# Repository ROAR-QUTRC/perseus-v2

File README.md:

> [!WARNING]
> This repository is now archived please see [perseus-v3](https://github.com/ROAR-QUTRC/perseus-v3/).

# perseus-v2

The main codebase for perseus starting 2024

## Documentation

Full documentation is located [here](https://roar-qutrc.github.io/)

## CI/CD Status

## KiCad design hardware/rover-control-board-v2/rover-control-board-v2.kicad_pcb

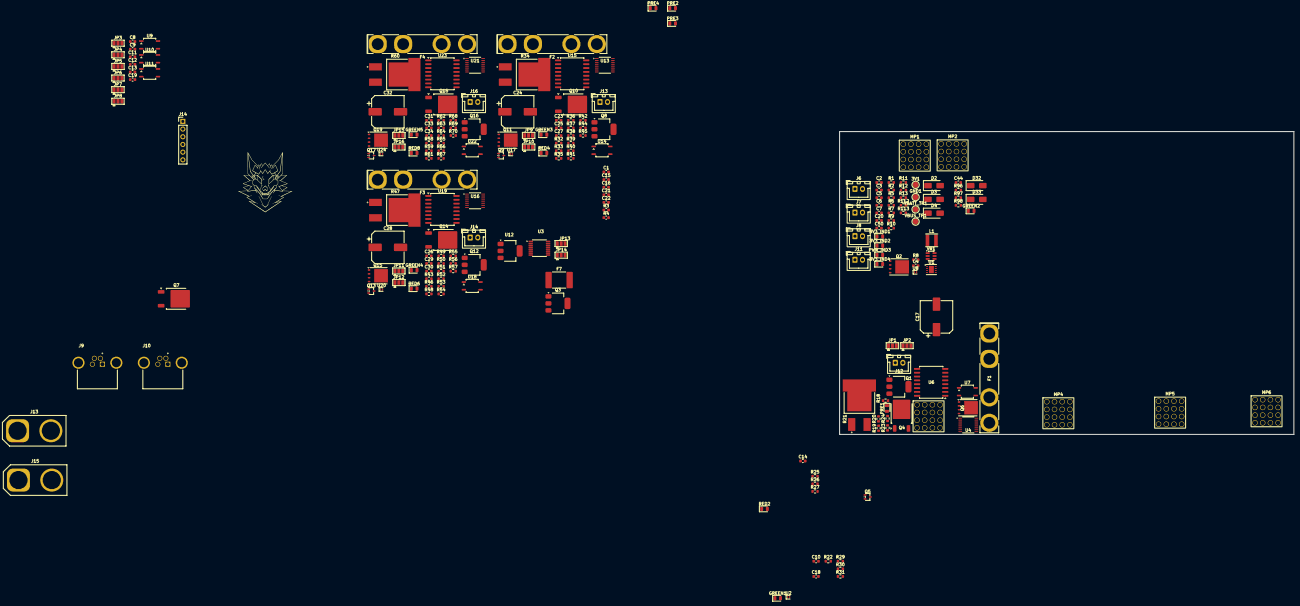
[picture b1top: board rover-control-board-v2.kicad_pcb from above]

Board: 4 copper layers, 150.0 x 100.0 mm, 216 parts (0 on the bottom side), 123 nets, no tracks yet.

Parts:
3V1: Testpoint; TestPoint_Pad_D2.0mm
3V3_IND1, 3V3_IND2, 3V3_IND4: 350-599; LED_0805_2012Metric
C1, C50: 4.7nF; C_0603_1608Metric
C2, C12, C13, C19: 10uF; C_0603_1608Metric
C3, C8, C9, C11, C16: 1uF; C_0603_1608Metric
C4, C5, C10, C14, C15, C18, C20, C23, C25, C26, C27, C29, C30, C31, C33, C34: 100nF; C_0603_1608Metric
C6, C7, C21, C22: 22uF; C_0603_1608Metric
C17, C24, C28, C32: C_Polarized; CP_Elec_10x10.5
C44: 10nF; C_0603_1608Metric
D2, D3: B160-E3; D_SMA
D4: 60V TVS; D_SMA
D32: US1M; D_SMA
D33: SMAZ12-13-F; D_SMA
F1, F2, F3, F4: Blade; Fuseholder_Keystone_3555-2
F7: 2A; Fuse_2920_7451Metric_Pad2.10x5.45mm_HandSolder
GND1: Testpoint; TestPoint_Pad_D2.0mm
GREEN1, GREEN2, GREEN3, GREEN4, GREEN5: 350-599; LED_0805_2012Metric
J6, J7, J8: CAN1; JST_XH_B2B-XH-A_1x02_P2.50mm_Vertical
J9, J10: M8 receptacle; Tensility_M8_Socket_4P_Shielded_A
J11: Contactor; JST_XH_B2B-XH-A_1x02_P2.50mm_Vertical
J12, J13#2, J14, J16: TEMP_PROBE; JST_XH_B2B-XH-A_1x02_P2.50mm_Vertical
J13: XT90; AMASS_XT90-F_1x02_P11.00mm_Vertical
J14#2: EXT_I_SENSE; PinHeader_1x06_P2.54mm_Vertical
J15: XT90_PWR; AMASS_XT90-F_1x02_P11.00mm_Vertical
JP1, JP9, JP11, JP15: ADDR1; SolderJumper-3_P1.3mm_Open_Pad1.0x1.5mm
JP2, JP10, JP12, JP16: ADDR2; SolderJumper-3_P1.3mm_Open_Pad1.0x1.5mm
JP3, JP4, JP5, JP6, JP7, JP8, JP13, JP14: ADDR; SolderJumper-3_P1.3mm_Open_Pad1.0x1.5mm
L1: HPC4018NF-4R7M; L_Taiyo-Yuden_MD-4040
MP1, MP2, MP3, MP4, MP5, MP6: Redcube Press Fit; MP_Wurth_WP-BUFU_7461097
PRE1, PRE2, PRE3, PRE4: 5991110147F; LED_0805_2012Metric
PWR_IND3: 350-599; LED_0805_2012Metric
Q1, Q3, Q8, Q12, Q16: NMOS_GDS; SOT-223
Q2, Q6, Q11, Q15, Q19: CSD19533Q5A; TDSON-8-1
Q4, Q7, Q10, Q14, Q18: Q_PMOS_GDS; TO-252-2
Q5, Q9, Q13, Q17: PMOS; SOT-323_SC-70
R1, R2: 223k; R_0603_1608Metric
R3, R4: 62R; C_0603_1608Metric
R5, R23, R24, R30, R37, R38, R45, R50, R51, R57, R63, R64, R70: 1k; R_0603_1608Metric
R6, R29, R44, R56, R69: 20k; R_0603_1608Metric
R7: 109k; R_0603_1608Metric
R8: 10k; C_0603_1608Metric
R9: 9.53M; R_0603_1608Metric
R10: 232k; R_0603_1608Metric
R11, R12, R20, R35, R48, R61, R97: 4.7k; R_0603_1608Metric
R13, R18, R25, R27, R31, R32, R36, R40, R41, R43, R49, R53, R54, R58, R62, R66, R67, R98: 10k; R_0603_1608Metric
R19, R26, R33, R39, R46, R52, R59, R65, R96: 100R; R_0603_1608Metric
R21, R34, R47, R60: 10R; RES_PWR263S-35-10R0F
R22, R42, R55, R68: 200R; R_0603_1608Metric
R112, R113: 62R; R_0603_1608Metric
RED2, RED4, RED6, RED8: 5991110147F; LED_0805_2012Metric
U1: max6496
U2, U8, U17, U20, U24: D3V3M1U2S9-7; D_SOD-882
U3: ADC128D818; TSSOP-16_4.4x5mm_P0.65mm
U4, U13, U16, U21: LM82
U6, U15, U19, U23: ACS37003; SOIC-16W_7.5x10.3mm_P1.27mm
U7, U14, U18, U22: VOM1271T; SOP-4_3.8x4.1mm_P2.54mm
U9, U10, U11: MCP3427T-E/UN; SOP-4_3.8x4.1mm_P2.54mm
U12: MCP1792x-5002xDB; SOT-223-3_TabPin2
VBATT_TP1: Testpoint; TestPoint_Pad_D2.0mm
VBUS_TP1: Testpoint; TestPoint_Pad_D2.0mm
VR1: AP63203WU-7; TSOT-23-6

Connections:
3V3: 3V1.1 (1_1), 3V3_IND1.2 (A), C6.1, C7.1, C8.2, C9.2, C11.2, C12.2, C13.2, C15.2, C16.1, C19.2, JP3.1 (A), JP4.1 (A), JP5.1 (A), JP6.1 (A), JP7.1 (A), JP8.1 (A), JP13.1 (A), JP14.1 (A), L1.2, R11.2, R12.2, U3.5 (V+), VR1.1 (FB)
+BATT: C28.1, D4.2 (A2), J15.2, MP1.1 (1_1), PWR_IND3.2 (A), Q15.5 (D), R6.2, R47.1, VBATT_TP1.1 (1_1)
/3v3: C14.2, C18.2, C23.2, C25.2, C26.2, C29.2, C31.2, C33.2, J14#2.6, JP1.1 (A), JP2.1 (A), JP9.1 (A), JP10.1 (A), JP11.1 (A), JP12.1 (A), JP15.1 (A), JP16.1 (A), RED2.2 (A), RED4.2 (A), RED6.2 (A), RED8.2 (A), U4.2 (VCC), U6.13 (VCC), U13.2 (VCC), U15.13 (VCC), U16.2 (VCC), U19.13 (VCC), U21.2 (VCC), U23.13 (VCC)
/CAN_H: J6.1, J7.1, J8.1, J10.2
/CAN_L: J6.2, J7.2, J8.2, J10.1
/JMP_PWR: C21.1, U12.1 (VI)
/SCLK: R11.1, U4.14 (SCLK), U13.14 (SCLK), U16.14 (SCLK), U21.14 (SCLK)
/SDATA: R12.1, U4.12 (SDATA), U13.12 (SDATA), U16.12 (SDATA), U21.12 (SDATA)
/TEMP_ALARM_: R26.2, R39.2, R52.2, R65.2, U4.16 (T_ALARM), U13.16 (T_ALARM), U16.16 (T_ALARM), U21.16 (T_ALARM)
/VBATT_sense: C20.2, R5.2, R6.1, U8.1 (K)
/aux_1_ctrl: GREEN3.2 (A), R42.1
/aux_1_pre_en: PRE2.2 (A), R33.1
/aux_1_v_sense: C27.1, R44.1, R45.2, U17.1 (K)
/comp_ctrl: GREEN1.2 (A), R22.1
/comp_pre_en: PRE1.2 (A), R19.1
/comp_v_sense: C10.1, R29.1, R30.2, U2.1 (K)
/comp_vi_out: U6.12 (VIOUT), U9.1 (CH1+)
/comp_vi_vref: U6.11 (VREF), U9.2 (CH1-)
/contactor/COIL_H: D32.1 (K), F7.2, GREEN2.2 (A), J11.1
/contactor/COIL_L: D33.1 (K), J11.2, Q3.2 (D), R98.2
/drive_1_ctrl: GREEN4.2 (A), R55.1
/drive_1_pre_en: PRE3.2 (A), R46.1
/drive_1_v_sense: C30.1, R56.1, R57.2, U20.1 (K)
/ext_ctrl: GREEN5.2 (A), R68.1
/ext_pre_en: PRE4.2 (A), R59.1
/power_bus_1/PWR_OUT: F1.1, J13.1, MP3.1 (1_1), Q4.3 (S), R29.2
/power_bus_2/PWR_OUT: F2.1, MP4.1 (1_1), Q10.3 (S), R44.2
/power_bus_3/PWR_OUT: F3.1, MP5.1 (1_1), Q14.3 (S), R56.2
/power_bus_4/PWR_OUT: F4.1, MP6.1 (1_1), Q18.3 (S), R69.2
/power_bus_4/V_sense: C34.1, R69.1, R70.2, U24.1 (K)
GND: C1.2, C2.2, C3.2, C4.2, C6.2, C7.2, C8.1, C9.1, C10.2, C11.1, C12.1, C13.1, C14.1, C15.1, C16.2, C17.2, C18.1, C19.1, C20.1, C21.2, C22.2, C23.1, C24.2, C25.1, C26.1, C27.2, C28.2, C29.1, C30.2, C31.1, C32.2, C33.1, C34.2, C44.2, C50.2, D4.1 (A1), GND1.1 (1_1), J13.2, J14#2.1, J15.1, JP1.3 (B), JP2.3 (B), JP3.3 (B), JP4.3 (B), JP5.3 (B), JP6.3 (B), JP7.3 (B), JP8.3 (B), JP9.3 (B), JP10.3 (B), JP11.3 (B), JP12.3 (B), JP13.3 (B), JP14.3 (B), JP15.3 (B), JP16.3 (B), Q1.3 (S), Q3.3 (S), Q5.3 (S), Q8.3 (S), Q9.3 (S), Q12.3 (S), Q13.3 (S), Q16.3 (S), Q17.3 (S), R1.2, R2.2, R5.1, R7.2, R10.2, R13.2, R18.1, R20.1, R27.2, R30.1, R31.1, R32.1, R35.1, R40.2, R41.1, R43.1, R45.1, R48.1, R53.2, R54.1, R57.1, R58.1, R61.1, R66.2, R67.1, R70.1, R97.1, U1.5 (GND), U2.2 (A), U3.4 (GND), U4.8 (GND), U6.16 (GND), U7.2, U8.2 (A), U9.3 (V_{SS}), U10.3 (V_{SS}), U11.3 (V_{SS}), U12.2 (GND), U13.8 (GND), U14.2, U15.16 (GND), U16.8 (GND), U17.2 (A), U18.2, U19.16 (GND), U20.2 (A), U21.8 (GND), U22.2, U23.16 (GND), U24.2 (A), VR1.4 (GND)
unnamed: 3V3_IND1.1 (K), R13.1
unnamed: 3V3_IND2.1 (K), R1.1
unnamed: 3V3_IND4.2 (A), C22.1, D3.2 (A), U12.3 (VO)
unnamed: 3V3_IND4.1 (K), R2.1
unnamed: C1.1, R3.1, R4.1
unnamed: C50.1, R112.1, R113.1
unnamed: C3.1, D2.1 (K), D3.1 (K)
unnamed: D32.2 (A), D33.2 (A)
unnamed: F1.2, U6.5 (IP-), U6.6 (IP-), U6.7 (IP-), U6.8 (IP-)
unnamed: F2.2, U15.5 (IP-), U15.6 (IP-), U15.7 (IP-), U15.8 (IP-)
unnamed: F3.2, U19.5 (IP-), U19.6 (IP-), U19.7 (IP-), U19.8 (IP-)
unnamed: F4.2, U23.5 (IP-), U23.6 (IP-), U23.7 (IP-), U23.8 (IP-)
unnamed: GREEN1.1 (K), R31.2
unnamed: GREEN2.1 (K), R98.1
unnamed: GREEN3.1 (K), R41.2
unnamed: GREEN4.1 (K), R54.2
unnamed: GREEN5.1 (K), R67.2
unnamed: J9.1, R112.2
unnamed: J9.2, R113.2
unnamed: J12.1, U4.4 (D-)
unnamed: J12.2, U4.3 (D+)
unnamed: J13#2.1, U13.4 (D-)
unnamed: J13#2.2, U13.3 (D+)
unnamed: J14.1, U16.4 (D-)
unnamed: J14.2, U16.3 (D+)
unnamed: J16.1, U21.4 (D-)
unnamed: J16.2, U21.3 (D+)
unnamed: JP1.2 (C), U4.10 (ADDR0)
unnamed: JP2.2 (C), U4.6 (ADDR1)
unnamed: JP9.2 (C), U13.10 (ADDR0)
unnamed: JP10.2 (C), U13.6 (ADDR1)
unnamed: JP11.2 (C), U16.10 (ADDR0)
unnamed: JP12.2 (C), U16.6 (ADDR1)
unnamed: JP13.2 (C), U3.8 (A1)
unnamed: JP14.2 (C), U3.7 (A0)
unnamed: JP15.2 (C), U21.10 (ADDR0)
unnamed: JP16.2 (C), U21.6 (ADDR1)
unnamed: PRE1.1 (K), R18.2
unnamed: PRE2.1 (K), R32.2
unnamed: PRE3.1 (K), R43.2
unnamed: PRE4.1 (K), R58.2
unnamed: PWR_IND3.1 (K), R7.1
unnamed: Q1.2 (D), R24.1
unnamed: Q1.1 (G), R19.2, R20.2
unnamed: Q2.5 (D), Q7.3 (S), R9.1, U1.1 (IN), U1.2 (_SHDN)
unnamed: Q2.4 (G), U1.6 (GATE)
unnamed: Q3.1 (G), R96.1, R97.2
unnamed: Q4.2 (D), R21.2, R23.2
unnamed: Q4.1 (G), R23.1, R24.2
unnamed: Q5.1 (D), R25.1
unnamed: Q5.2 (G), R26.1, R27.1
unnamed: Q6.4 (G), U7.4
unnamed: Q6.1 (S), Q6.2 (S), Q6.3 (S), U6.1 (IP+), U6.2 (IP+), U6.3 (IP+), U6.4 (IP+), U7.3
unnamed: MP2.1 (1_1), Q7.2 (D), VBUS_TP1.1 (1_1)
unnamed: Q7.1 (G), U1.4 (GATEP)
unnamed: Q8.2 (D), R38.1
unnamed: Q8.1 (G), R33.2, R35.2
unnamed: Q9.1 (D), R36.1
unnamed: Q9.2 (G), R39.1, R40.1
unnamed: Q10.2 (D), R34.2, R37.2
unnamed: Q10.1 (G), R37.1, R38.2
unnamed: Q11.4 (G), U14.4
unnamed: Q11.1 (S), Q11.2 (S), Q11.3 (S), U14.3, U15.1 (IP+), U15.2 (IP+), U15.3 (IP+), U15.4 (IP+)
unnamed: Q12.2 (D), R51.1
unnamed: Q12.1 (G), R46.2, R48.2
unnamed: Q13.1 (D), R49.1
unnamed: Q13.2 (G), R52.1, R53.1
unnamed: Q14.2 (D), R47.2, R50.2
unnamed: Q14.1 (G), R50.1, R51.2
unnamed: Q15.4 (G), U18.4
unnamed: Q15.1 (S), Q15.2 (S), Q15.3 (S), U18.3, U19.1 (IP+), U19.2 (IP+), U19.3 (IP+), U19.4 (IP+)
unnamed: Q16.2 (D), R64.1
unnamed: Q16.1 (G), R59.2, R61.2
unnamed: Q17.1 (D), R62.1
unnamed: Q17.2 (G), R65.1, R66.1
unnamed: Q18.2 (D), R60.2, R63.2
unnamed: Q18.1 (G), R63.1, R64.2
unnamed: Q19.4 (G), U22.4
unnamed: Q19.1 (S), Q19.2 (S), Q19.3 (S), U22.3, U23.1 (IP+), U23.2 (IP+), U23.3 (IP+), U23.4 (IP+)
unnamed: R22.2, U7.1
unnamed: R42.2, U14.1
unnamed: R55.2, U18.1
unnamed: R68.2, U22.1
unnamed: R25.2, RED2.1 (K)
unnamed: R36.2, RED4.1 (K)
unnamed: R49.2, RED6.1 (K)
unnamed: R62.2, RED8.1 (K)
unnamed: R9.2, R10.1, U1.3 (OVSET)
unnamed: C5.2, VR1.6 (BST)
unnamed: C4.1, R8.2, VR1.2 (EN)
unnamed: C5.1, L1.1, VR1.5 (SW)
VBUS: 3V3_IND2.2 (A), C2.1, C17.1, C24.1, C32.1, C44.1, D2.2 (A), F7.1, J14#2.4, Q2.1 (S), Q2.2 (S), Q2.3 (S), Q6.5 (D), Q11.5 (D), Q19.5 (D), R8.1, R21.1, R34.1, R60.1, U1.7 (OUTFB), VR1.3 (IN)

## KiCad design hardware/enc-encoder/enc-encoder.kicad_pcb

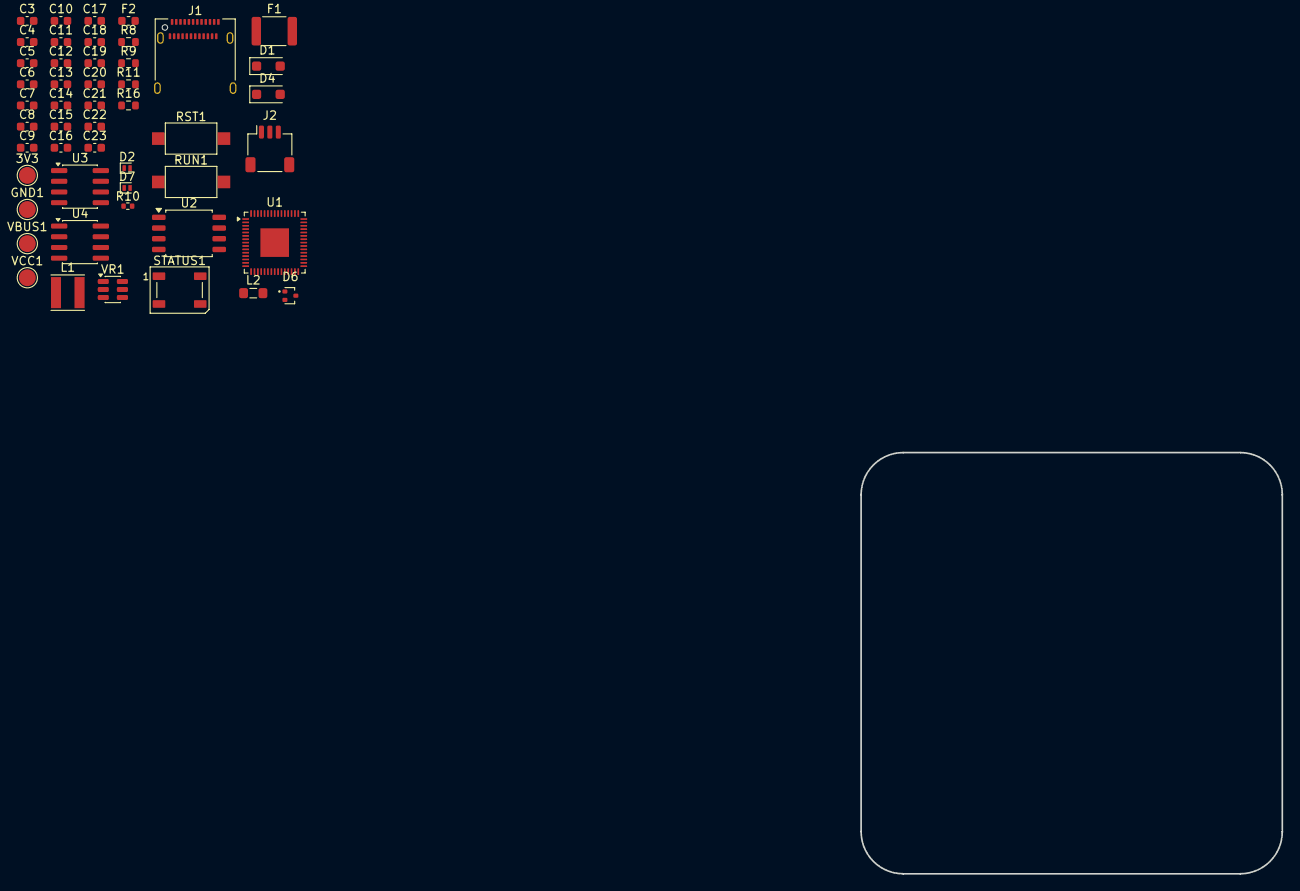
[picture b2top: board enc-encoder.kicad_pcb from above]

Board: 4 copper layers, 50.0 x 50.0 mm, 49 parts (0 on the bottom side), 23 nets, no tracks yet.

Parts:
3V3: Testpoint; TestPoint_Pad_D2.0mm
C3, C7, C8, C9, C10, C11, C12, C13, C14, C15, C16, C17, C22, C23: 100nF; C_0603_1608Metric
C4: 10uF; C_0603_1608Metric
C5, C6: 22uF; C_0603_1608Metric
C18, C19, C20, C21: 4.7uF; C_0603_1608Metric
D1, D4: DSS14UTR; D_SOD-123F
D2, D7: PESD1; D_SOD-882
D6: ESDA5V3L; SOT-416
F1: 500mA PTC fuse; Fuse_1812_4532Metric
F2: 500mA fast-blow fuse; Fuse_0603_1608Metric
GND1: Testpoint; TestPoint_Pad_D2.0mm
J1: USB_C_Receptacle; USB_C_Receptacle_Amphenol_12401610E4-2A
J2: SM03B-SRSS-TB; JST_SH_SM03B-SRSS-TB_1x03-1MP_P1.00mm_Horizontal
L1: HPC4018NF-4R7M; L_Taiyo-Yuden_MD-4040
L2: 3.3uH; L_0805_2012Metric_Pad1.05x1.20mm_HandSolder
R8: 470R; R_0603_1608Metric
R9, R11, R16: 10k; R_0603_1608Metric
R10: 10k; R_0402_1005Metric
RST1: RST; SW_SPST_CK_RS282G05A3
RUN1: RST; SW_SPST_CK_RS282G05A3
STATUS1: 16347; LED_WS2812B_PLCC4_5.0x5.0mm_P3.2mm
U1: RP2350A; QFN-60-1EP_7x7mm_P0.4mm_EP3.4x3.4mm
U2: W25Q128JVS; SOIC-8_5.3x5.3mm_P1.27mm
U3: SP3485CN; SOIC-8_3.9x4.9mm_P1.27mm
U4: SOIC-8_3.9x4.9mm_P1.27mm
VBUS1: Testpoint; TestPoint_Pad_D2.0mm
VCC1: Testpoint; TestPoint_Pad_D2.0mm
VR1: AP63203WU-7; TSOT-23-6

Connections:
3V3: 3V3.1 (1_1), C5.1, C6.1, C8.1, C9.1, C10.1, C11.1, C12.1, C13.1, C14.1, C15.1, C20.1, C22.1, C23.1, L1.2, STATUS1.1 (VDD), U1.1 (IOVDD), U1.11 (IOVDD), U1.20 (IOVDD), U1.30 (IOVDD), U1.38 (IOVDD), U1.44 (ADC_AVDD), U1.45 (IOVDD), U1.49 (VREG_VIN), U1.53 (USB_OTP_VDD), U1.54 (QSPI_IOVDD), U2.8 (VCC), U4.1 (VDD5V), U4.2 (VDD3V), VR1.1 (FB)
+1V1: C16.1, C17.1, C18.1, C21.1, L2.1, U1.6 (DVDD), U1.23 (DVDD), U1.39 (DVDD), U1.50 (VREG_FB)
/SWCLK: J2.1, U1.24 (SWCLK)
/USB_D_N: D6.1 (K1), J1.A7 (D-), J1.B7 (D-)
/USB_D_P: D6.2 (K2), J1.A6 (D+), J1.B6 (D+)
/uC_LED: R8.1, R16.1
GND: C4.2, C5.2, C6.2, C7.2, C8.2, C9.2, C10.2, C11.2, C12.2, C13.2, C14.2, C15.2, C16.2, C17.2, C18.2, C19.2, C20.2, C21.2, C22.2, C23.2, D2.2 (A2), D6.3 (A), D7.2 (A2), GND1.1 (1_1), J1.A1 (GND), J1.A12 (GND), J1.B1 (GND), J1.B12 (GND), J2.2, J2.3, J2.MP (MountPin), R9.2, R11.2, R16.2, RST1.2, RUN1.2, STATUS1.3 (VSS), U1.25 (SWDIO), U1.47 (VREG_PGND), U1.61 (GND), U2.4 (GND), U4.4 (GND), VR1.4 (GND)
unnamed: D1.1 (K), F1.2
unnamed: D4.1 (K), F2.1
unnamed: R8.2, STATUS1.4 (DIN)
unnamed: U1.56 (QSPI_SCLK), U2.6 (CLK)
unnamed: U1.57 (QSPI_SD0), U2.5 (DI/IO_{0})
unnamed: U1.59 (QSPI_SD1), U2.2 (DO/IO_{1})
unnamed: U1.58 (QSPI_SD2), U2.3 (~WP/IO_{2})
unnamed: U1.55 (QSPI_SD3), U2.7 (~HOLD/~RESET/IO_{3})
unnamed: C19.1, U1.46 (VREG_AVDD)
unnamed: L2.2, U1.48 (VREG_LX)
unnamed: C3.2, VR1.6 (BST)
unnamed: C7.1, R10.2, VR1.2 (EN)
unnamed: C4.1, F1.1, F2.2, R10.1, VCC1.1 (1_1), VR1.3 (IN)
unnamed: C3.1, L1.1, VR1.5 (SW)
VBUS: D2.1 (A1), D4.2 (A), J1.A4 (VBUS), J1.A9 (VBUS), J1.B4 (VBUS), J1.B9 (VBUS), VBUS1.1 (1_1)
VIN: D1.2 (A), D7.1 (A1)

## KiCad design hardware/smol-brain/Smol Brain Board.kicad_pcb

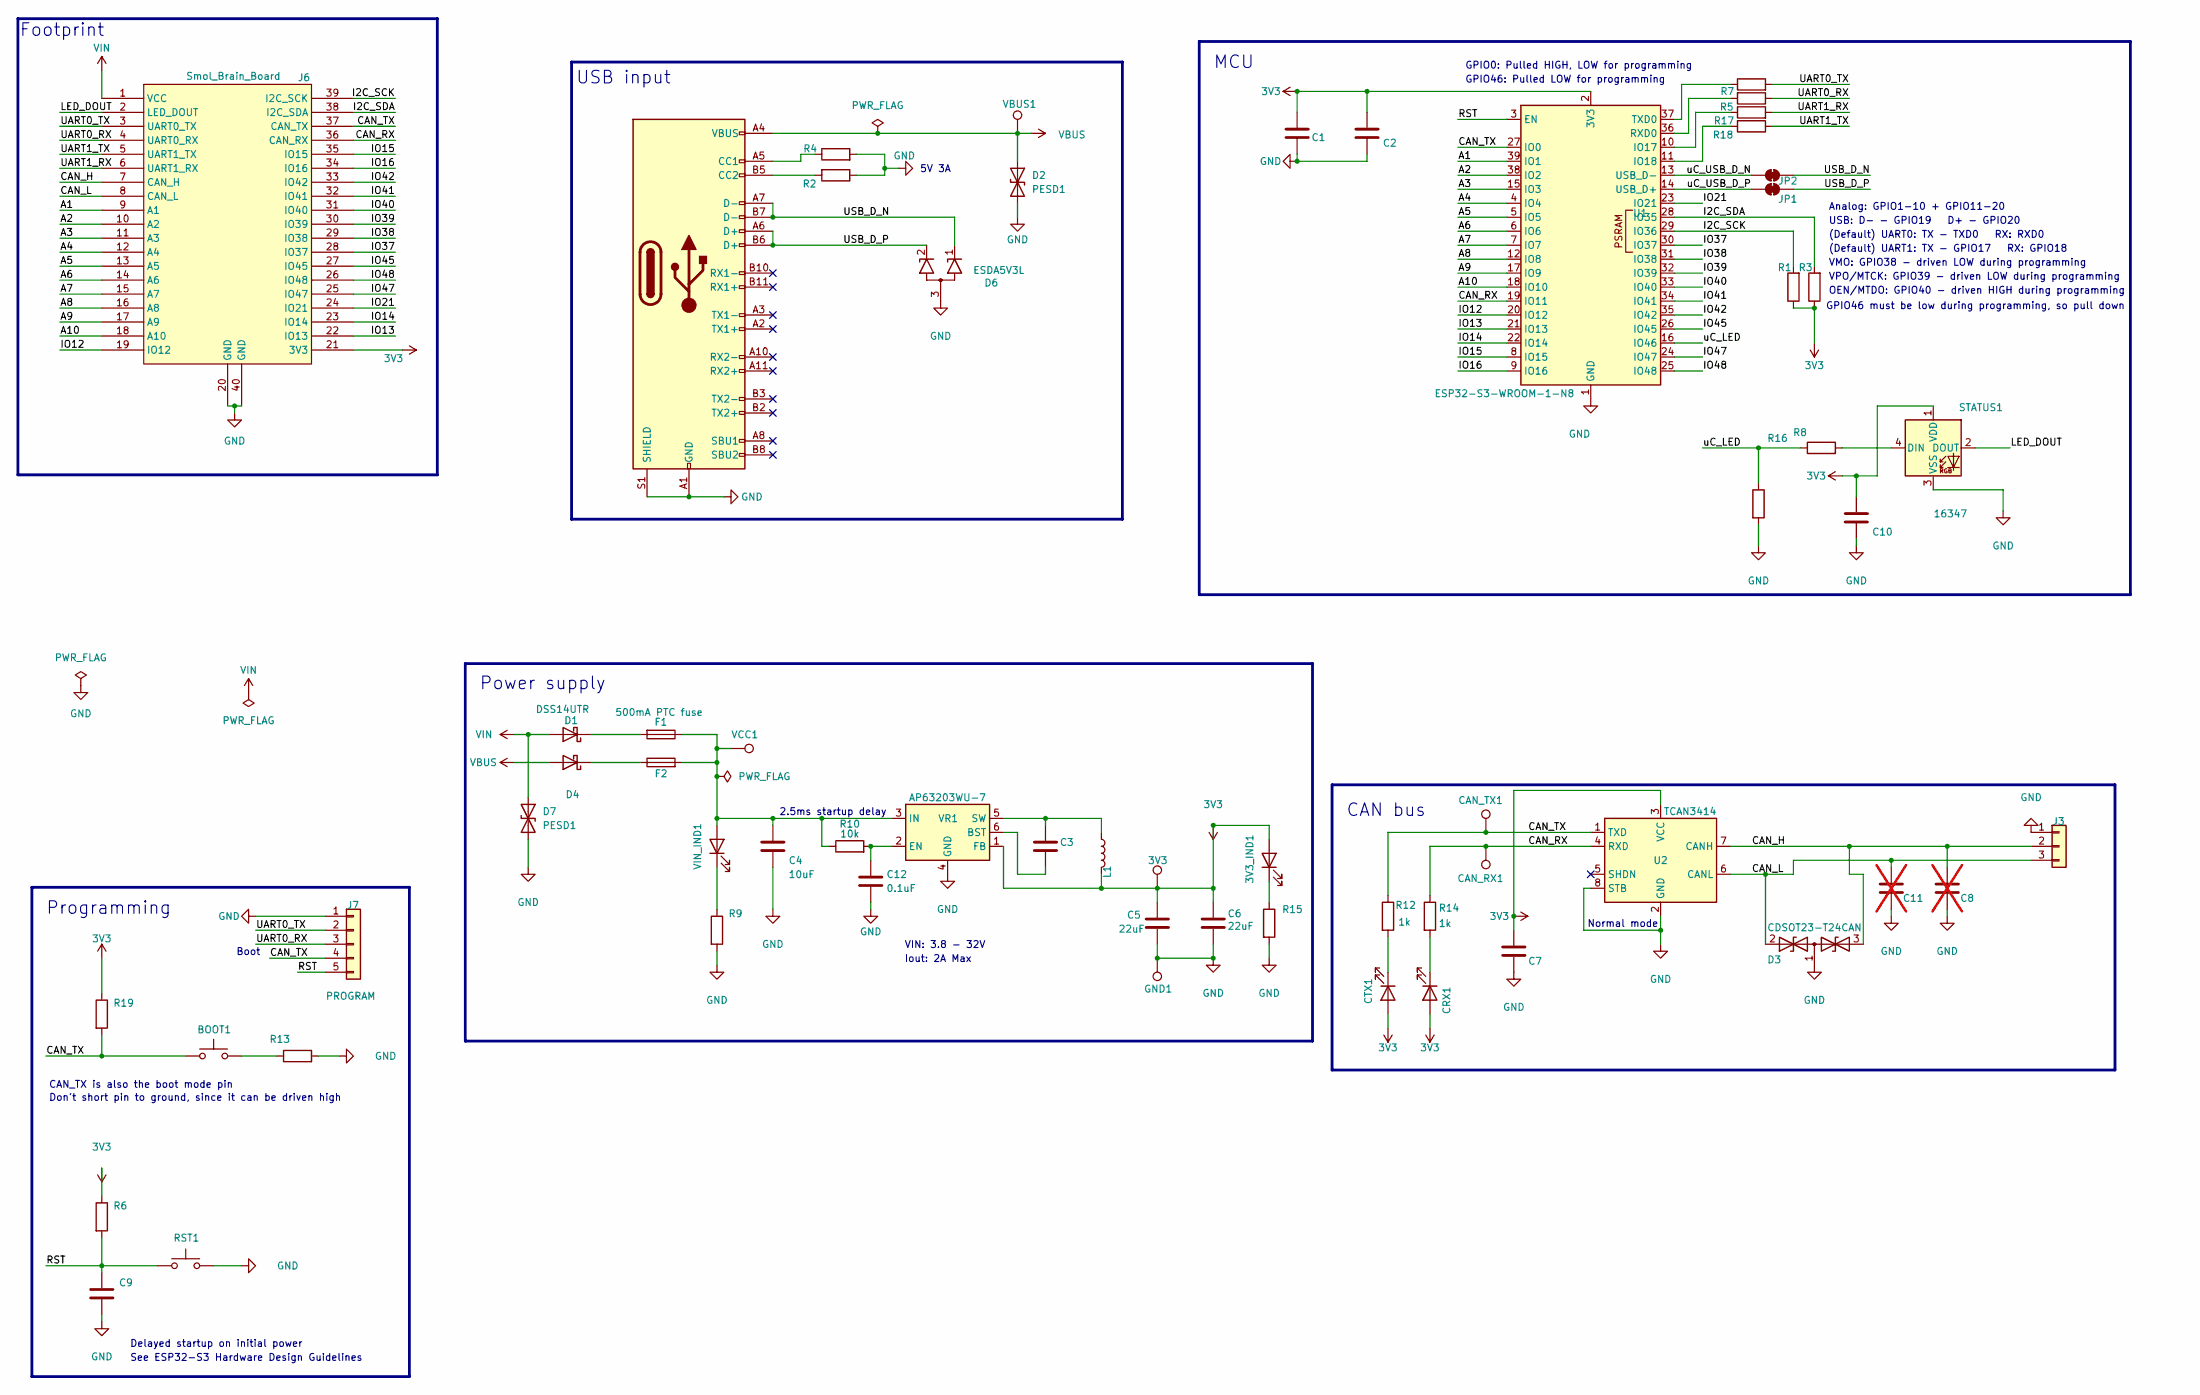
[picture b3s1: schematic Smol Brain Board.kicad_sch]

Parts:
3V3: Testpoint; TestPoint_Pad_D2.0mm
3V3_IND1: LTST-C190KRKT; LED_0603_1608Metric; manufactuer part number LTST-C190KRKT
BOOT1: BOOT; SW_SPST_CK_RS282G05A3; manufactuer part number GSPTS004302
C1: Capacitor 10u 16V 0805; C_0805_2012Metric; manufactuer part number CL21B106KOQNNNE
C2, C3, C7, C10: Capacitor 100n 50V 0603; C_0603_1608Metric; manufactuer part number CL10F104ZB8NNNC
C4: 10uF; C_0603_1608Metric; manufactuer part number CL10A106KP8NNNC
C5, C6: 22uF; C_0603_1608Metric; manufactuer part number CL10A226MP8NUNE
C8, C11: Capacitor Placeholder 0603; C_0603_1608Metric; not fitted
C9: Capacitor 1u 25V; C_0603_1608Metric; manufactuer part number CL10B105KA8NNNC
C12: 0.1uF; C_0402_1005Metric; manufactuer part number CL05B104KB5NNNC
CAN_RX1: Testpoint; TestPoint_Pad_D2.0mm
CAN_TX1: Testpoint; TestPoint_Pad_D2.0mm
CRX1: LTST-C190GKT; LED_0603_1608Metric; manufactuer part number LTST-C190KRKT
CTX1: LTST-C190KSKT; LED_0603_1608Metric; manufactuer part number LTST-C190KRKT
D1, D4: DSS14UTR; D_SOD-123F; manufactuer part number DSS14U
D2, D7: PESD1; D_SOD-882; manufactuer part number PESD1CANFD33L-QYL
D3: CDSOT23-T24CAN; SOT-23; manufactuer part number CDSOT23-T24CAN
D6: ESDA5V3L; SOT-416; manufactuer part number ESDA5V3L
F1: 500mA PTC fuse; Fuse_1812_4532Metric; manufactuer part number SMD1812B050TF/30
F2: 500mA fast-blow fuse; Fuse_0603_1608Metric; manufactuer part number SF-0603S050-2
GND1: Testpoint; TestPoint_Pad_D2.0mm
J1: USB_C_Receptacle; USB_C_Receptacle_Amphenol_12401610E4-2A; manufactuer part number 12401610E4#2A
J3: CAN_DBG; JST_XH_B3B-XH-A_1x03_P2.50mm_Vertical; manufactuer part number B3B-XH-A
J6: Smol_Brain_Board
J7: PROGRAM; PinHeader_1x05_P2.54mm_Vertical
JP1, JP2: SolderJumper_2_Bridged; SolderJumper-2_P1.3mm_Bridged_RoundedPad1.0x1.5mm
L1: HPC4018NF-4R7M; L_Taiyo-Yuden_MD-4040; manufactuer part number HPC 4018NF-4R7M
R1, R3: 4.7k; R_0402_1005Metric; manufactuer part number RC0402JR-074K7L
R2, R4: Resistor 5.1k; R_0402_1005Metric; manufactuer part number RC0402JR-075K1L
R5, R7: Resistor 1k 0603; R_0603_1608Metric; manufactuer part number RMCF0603FT1K00
R6, R10: 10k; R_0402_1005Metric; manufactuer part number RC1005F103CS
R8: Resistor 470R 0603; R_0603_1608Metric; manufactuer part number RC0603JR-07470RL
R9, R15, R16: Resistor 10k 0603; R_0603_1608Metric; manufactuer part number RC0603FR-0710KL
R12, R14: 1k; R_0402_1005Metric; manufactuer part number RC0402JR-071KL
R13: 100R; R_0402_1005Metric; manufactuer part number RC0402FR-07100RL
R17, R18: Resistor 1k 0603; R_0402_1005Metric; manufactuer part number RC0402JR-071KL
R19: Resistor 10k 0603; R_0402_1005Metric; manufactuer part number RC0603FR-0710KL
RST1: RST; SW_SPST_CK_RS282G05A3; manufactuer part number GSPTS004302
STATUS1: 16347; LED_WS2812B_PLCC4_5.0x5.0mm_P3.2mm; manufactuer part number 16347
U1: ESP32-S3-WROOM-1-N8; ESP32-S3-WROOM-1; manufactuer part number ESP32-S3-WROOM-1-N8
U2: TCAN3414; manufactuer part number TCAN3414DDFR
VBUS1: Testpoint; TestPoint_Pad_D2.0mm
VCC1: Testpoint; TestPoint_Pad_D2.0mm
VIN_IND1: LTST-C190KRKT; LED_0603_1608Metric; manufactuer part number LTST-C190KRKT
VR1: AP63203WU-7; TSOT-23-6; manufactuer part number AP63203WU-7

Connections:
3V3: 3V3.1, 3V3_IND1.2 (A), C1.2, C2.2, C5.1, C6.1, C7.1, C10.1, CRX1.2 (A), CTX1.2 (A), J6.21 (3V3), L1.2, R1.1, R3.1, R6.1, R19.1, STATUS1.1 (VDD), U1.2 (3V3), U2.3 (VCC), VR1.1 (FB)
/A1: J6.9 (A1), U1.39 (IO1)
/A2: J6.10 (A2), U1.38 (IO2)
/A3: J6.11 (A3), U1.15 (IO3)
/A4: J6.12 (A4), U1.4 (IO4)
/A5: J6.13 (A5), U1.5 (IO5)
/A6: J6.14 (A6), U1.6 (IO6)
/A7: J6.15 (A7), U1.7 (IO7)
/A8: J6.16 (A8), U1.12 (IO8)
/A9: J6.17 (A9), U1.17 (IO9)
/A10: J6.18 (A10), U1.18 (IO10)
/CAN_H: C8.1, D3.3 (A2), J3.2, J6.7 (CAN_H), U2.7 (CANH)
/CAN_L: C11.1, D3.2 (A1), J3.3, J6.8 (CAN_L), U2.6 (CANL)
/CAN_RX: CAN_RX1.1, J6.36 (CAN_RX), R14.1, U1.19 (IO11), U2.4 (RXD)
/CAN_TX: BOOT1.1, CAN_TX1.1, J6.37 (CAN_TX), J7.4, R12.1, R19.2, U1.27 (IO0), U2.1 (TXD)
/I2C_SCK: J6.39 (I2C_SCK), R1.2, U1.29 (IO36)
/I2C_SDA: J6.38 (I2C_SDA), R3.2, U1.28 (IO35)
/IO12: J6.19 (IO12), U1.20 (IO12)
/IO13: J6.22 (IO13), U1.21 (IO13)
/IO14: J6.23 (IO14), U1.22 (IO14)
/IO15: J6.35 (IO15), U1.8 (IO15)
/IO16: J6.34 (IO16), U1.9 (IO16)
/IO21: J6.24 (IO21), U1.23 (IO21)
/IO37: J6.28 (IO37), U1.30 (IO37)
/IO38: J6.29 (IO38), U1.31 (IO38)
/IO39: J6.30 (IO39), U1.32 (IO39)
/IO40: J6.31 (IO40), U1.33 (IO40)
/IO41: J6.32 (IO41), U1.34 (IO41)
/IO42: J6.33 (IO42), U1.35 (IO42)
/IO45: J6.27 (IO45), U1.26 (IO45)
/IO47: J6.25 (IO47), U1.24 (IO47)
/IO48: J6.26 (IO48), U1.25 (IO48)
/LED_DOUT: J6.2 (LED_DOUT), STATUS1.2 (DOUT)
/RST: C9.1, J7.5, R6.2, RST1.1, U1.3 (EN)
/UART0_RX: J6.4 (UART0_RX), J7.3, R5.1
/UART0_TX: J6.3 (UART0_TX), J7.2, R7.2
/UART1_RX: J6.6 (UART1_RX), R17.2
/UART1_TX: J6.5 (UART1_TX), R18.1
/USB_D_N: D6.1 (K1), J1.A7 (D-), J1.B7 (D-), JP2.2 (B)
/USB_D_P: D6.2 (K2), J1.A6 (D+), J1.B6 (D+), JP1.2 (B)
/uC_LED: R8.1, R16.1, U1.16 (IO46)
/uC_USB_D_N: JP2.1 (A), U1.13 (USB_D-)
/uC_USB_D_P: JP1.1 (A), U1.14 (USB_D+)
GND: C1.1, C2.1, C4.2, C5.2, C6.2, C7.2, C8.2, C9.2, C10.2, C11.2, C12.2, D2.2 (A2), D3.1 (common), D6.3 (A), D7.2 (A2), GND1.1, J1.A1 (GND), J1.A12 (GND), J1.B1 (GND), J1.B12 (GND), J1.S1 (SHIELD), J3.1, J6.20 (GND), J6.40 (GND), J7.1, R2.1, R4.2, R9.2, R13.2, R15.2, R16.2, RST1.2, STATUS1.3 (VSS), U1.1 (GND), U1.40 (GND), U1.41 (GND), U2.2 (GND), U2.8 (STB), VR1.4 (GND)
unnamed: 3V3_IND1.1 (K), R15.1
unnamed: BOOT1.2, R13.1
unnamed: CRX1.1 (K), R14.2
unnamed: CTX1.1 (K), R12.2
unnamed: D1.1 (K), F1.2
unnamed: D4.1 (K), F2.1
unnamed: J1.A5 (CC1), R4.1
unnamed: J1.B5 (CC2), R2.2
unnamed: R8.2, STATUS1.4 (DIN)
unnamed: R17.1, U1.10 (IO17)
unnamed: R18.2, U1.11 (IO18)
unnamed: R5.2, U1.36 (RXD0)
unnamed: R7.1, U1.37 (TXD0)
unnamed: C4.1, F1.1, F2.2, R10.1, VCC1.1, VIN_IND1.2 (A), VR1.3 (IN)
unnamed: R9.1, VIN_IND1.1 (K)
unnamed: C3.2, VR1.6 (BST)
unnamed: C12.1, R10.2, VR1.2 (EN)
unnamed: C3.1, L1.1, VR1.5 (SW)
VBUS: D2.1 (A1), D4.2 (A), J1.A4 (VBUS), J1.A9 (VBUS), J1.B4 (VBUS), J1.B9 (VBUS), VBUS1.1
VIN: D1.2 (A), D7.1 (A1), J6.1 (VCC)

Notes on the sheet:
USB: D- - GPIO19 D+ - GPIO20
Don't short pin to ground, since it can be driven high
GPIO46: Pulled LOW for programming
CAN_TX is also the boot mode pin
(Default) UART0: TX - TXD0 RX: RXD0
(Default) UART1: TX - GPIO17 RX: GPIO18
See ESP32-S3 Hardware Design Guidelines
Analog: GPIO1-10 + GPIO11-20
CAN bus
Normal mode
OEN/MTDO: GPIO40 - driven HIGH during programming
Delayed startup on initial power
Boot
2.5ms startup delay
MCU
VPO/MTCK: GPIO39 - driven LOW during programming
GPIO0: Pulled HIGH, LOW for programming
Iout: 2A Max
VMO: GPIO38 - driven LOW during programming
Programming
GPIO46 must be low during programming, so pull down
Power supply
USB input
5V 3A
Footprint
VIN: 3.8 - 32V

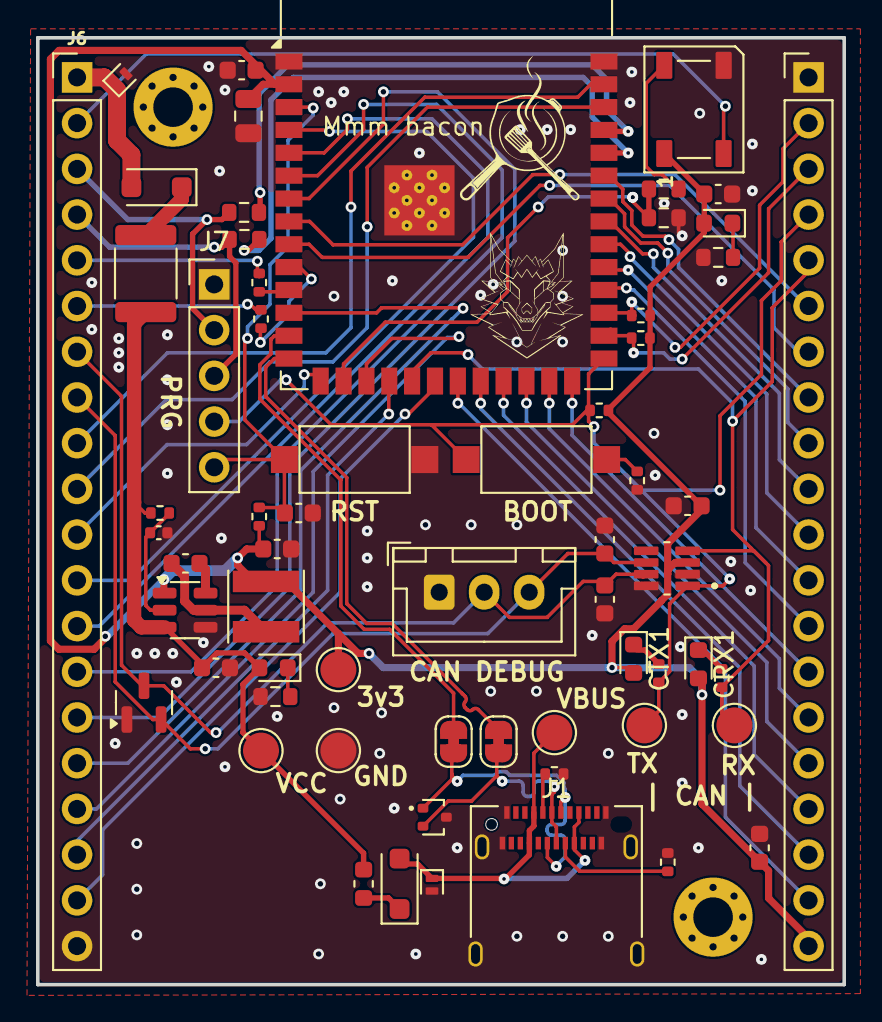
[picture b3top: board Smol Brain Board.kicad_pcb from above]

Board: 2 copper layers, 44.8 x 52.6 mm, 61 parts (0 on the bottom side), 64 nets.

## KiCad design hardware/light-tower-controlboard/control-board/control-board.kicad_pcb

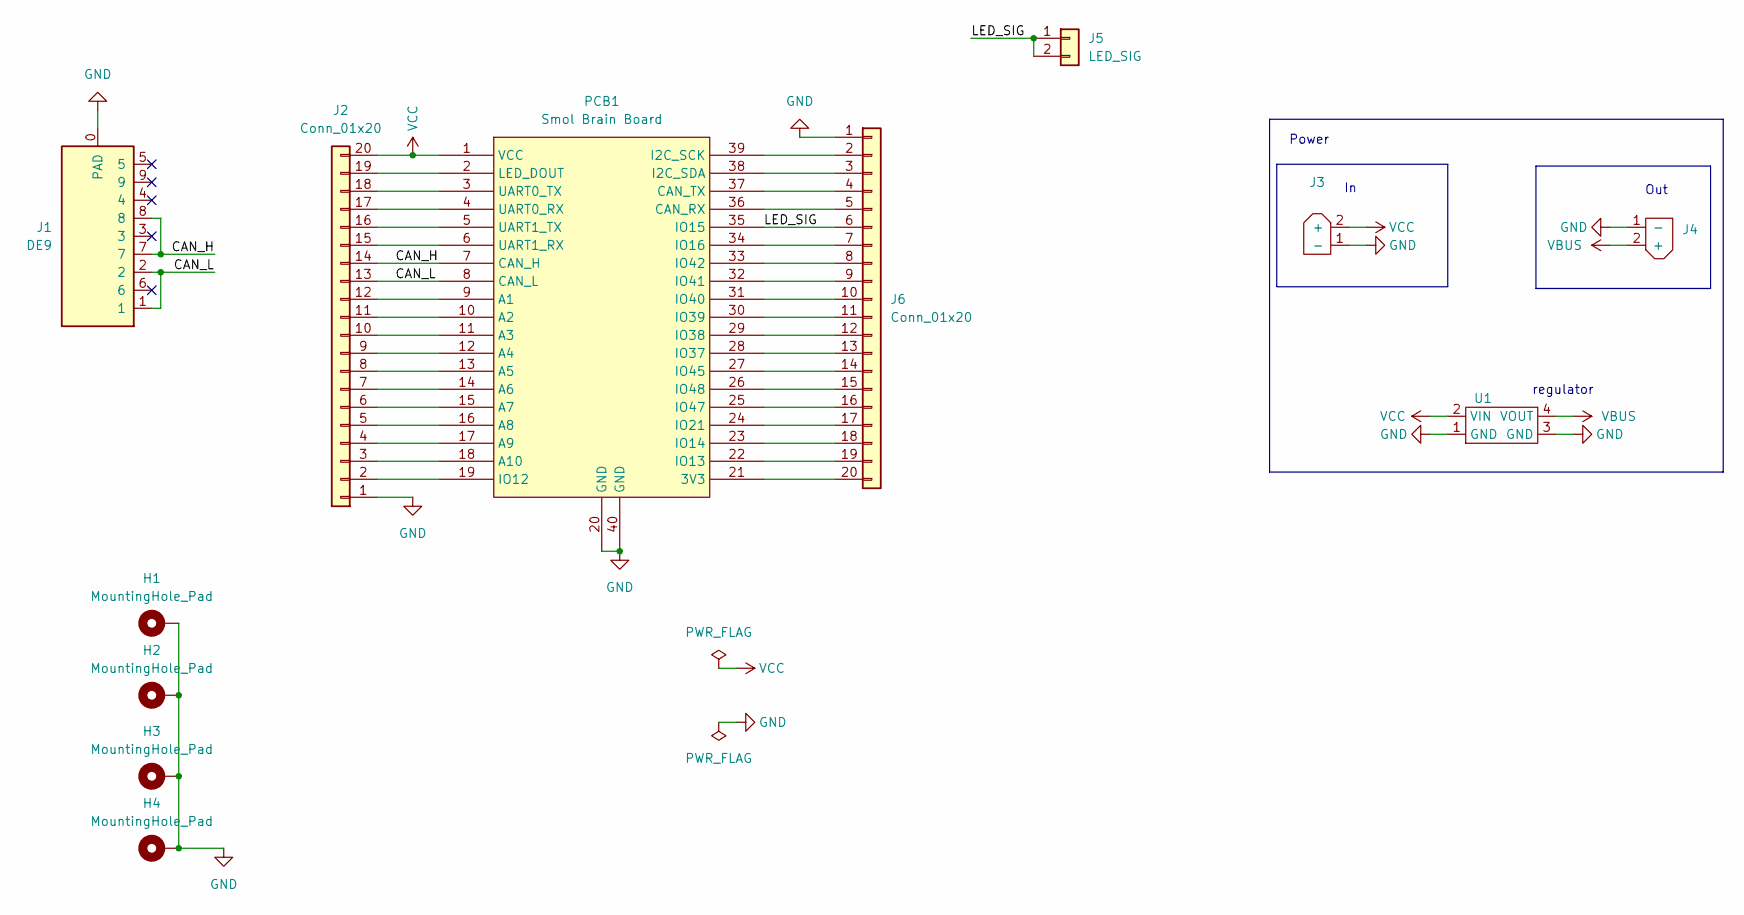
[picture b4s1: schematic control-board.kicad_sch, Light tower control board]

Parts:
H1, H2, H3, H4: MountingHole_Pad; MountingHole_3mm_Pad
J1: DE9; A-DF_09_A_KG-T2S
J2, J6: Conn_01x20; PinSocket_1x20_P2.54mm_Vertical
J3: AMASS_XT30PW-M_1x02_P2.50mm_Horizontal
J4: AMASS_XT30U-F_1x02_P5.0mm_Vertical
J5: LED_SIG; JST_XH_B2B-XH-AM_1x02_P2.50mm_Vertical
PCB1: Smol Brain Board; Smol_Brain_Board
U1: LM2596_reg_module

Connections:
/CAN_H: J1.7, J1.8, J2.14, PCB1.7 (CAN_H)
/CAN_L: J1.1, J1.2, J2.13, PCB1.8 (CAN_L)
/LED_SIG: J5.1, J5.2, J6.6, PCB1.35 (IO15)
GND: H1.1, H2.1, H3.1, H4.1, J1.0 (PAD), J2.1, J3.1 (-), J4.1 (-), J6.1, PCB1.20 (GND), PCB1.40 (GND), U1.1 (GND), U1.3 (GND)
unnamed: J2.2, PCB1.19 (IO12)
unnamed: J2.3, PCB1.18 (A10)
unnamed: J2.4, PCB1.17 (A9)
unnamed: J2.5, PCB1.16 (A8)
unnamed: J2.6, PCB1.15 (A7)
unnamed: J2.7, PCB1.14 (A6)
unnamed: J2.8, PCB1.13 (A5)
unnamed: J2.9, PCB1.12 (A4)
unnamed: J2.10, PCB1.11 (A3)
unnamed: J2.11, PCB1.10 (A2)
unnamed: J2.12, PCB1.9 (A1)
unnamed: J2.15, PCB1.6 (UART1_RX)
unnamed: J2.16, PCB1.5 (UART1_TX)
unnamed: J2.17, PCB1.4 (UART0_RX)
unnamed: J2.18, PCB1.3 (UART0_TX)
unnamed: J2.19, PCB1.2 (LED_DOUT)
unnamed: J6.2, PCB1.39 (I2C_SCK)
unnamed: J6.3, PCB1.38 (I2C_SDA)
unnamed: J6.4, PCB1.37 (CAN_TX)
unnamed: J6.5, PCB1.36 (CAN_RX)
unnamed: J6.7, PCB1.34 (IO16)
unnamed: J6.8, PCB1.33 (IO42)
unnamed: J6.9, PCB1.32 (IO41)
unnamed: J6.10, PCB1.31 (IO40)
unnamed: J6.11, PCB1.30 (IO39)
unnamed: J6.12, PCB1.29 (IO38)
unnamed: J6.13, PCB1.28 (IO37)
unnamed: J6.14, PCB1.27 (IO45)
unnamed: J6.15, PCB1.26 (IO48)
unnamed: J6.16, PCB1.25 (IO47)
unnamed: J6.17, PCB1.24 (IO21)
unnamed: J6.18, PCB1.23 (IO14)
unnamed: J6.19, PCB1.22 (IO13)
unnamed: J6.20, PCB1.21 (3V3)
VBUS: J4.2 (+), U1.4 (VOUT)
VCC: J2.20, J3.2 (+), PCB1.1 (VCC), U1.2 (VIN)

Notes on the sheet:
regulator
Power
Out

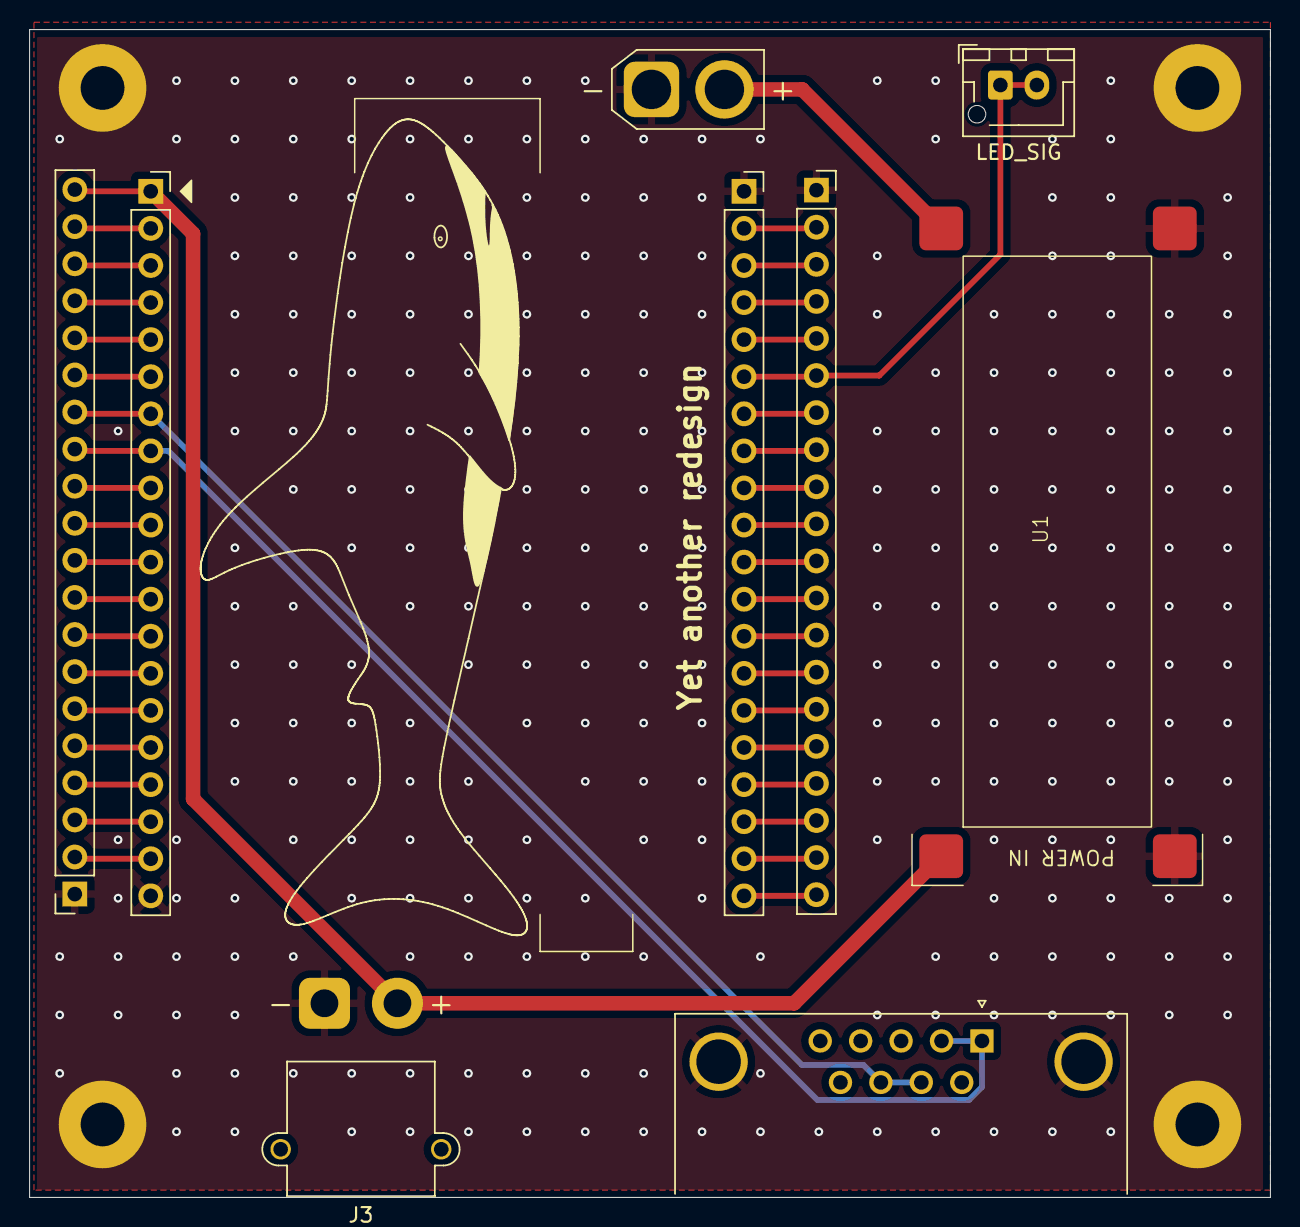
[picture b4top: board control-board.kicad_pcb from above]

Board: 2 copper layers, 85.0 x 80.0 mm, 12 parts (0 on the bottom side), 40 nets.

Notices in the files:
parts and their libraries:
COPYRIGHT: Copyright (C) 2023 Ultra Librarian. All rights reserved.
